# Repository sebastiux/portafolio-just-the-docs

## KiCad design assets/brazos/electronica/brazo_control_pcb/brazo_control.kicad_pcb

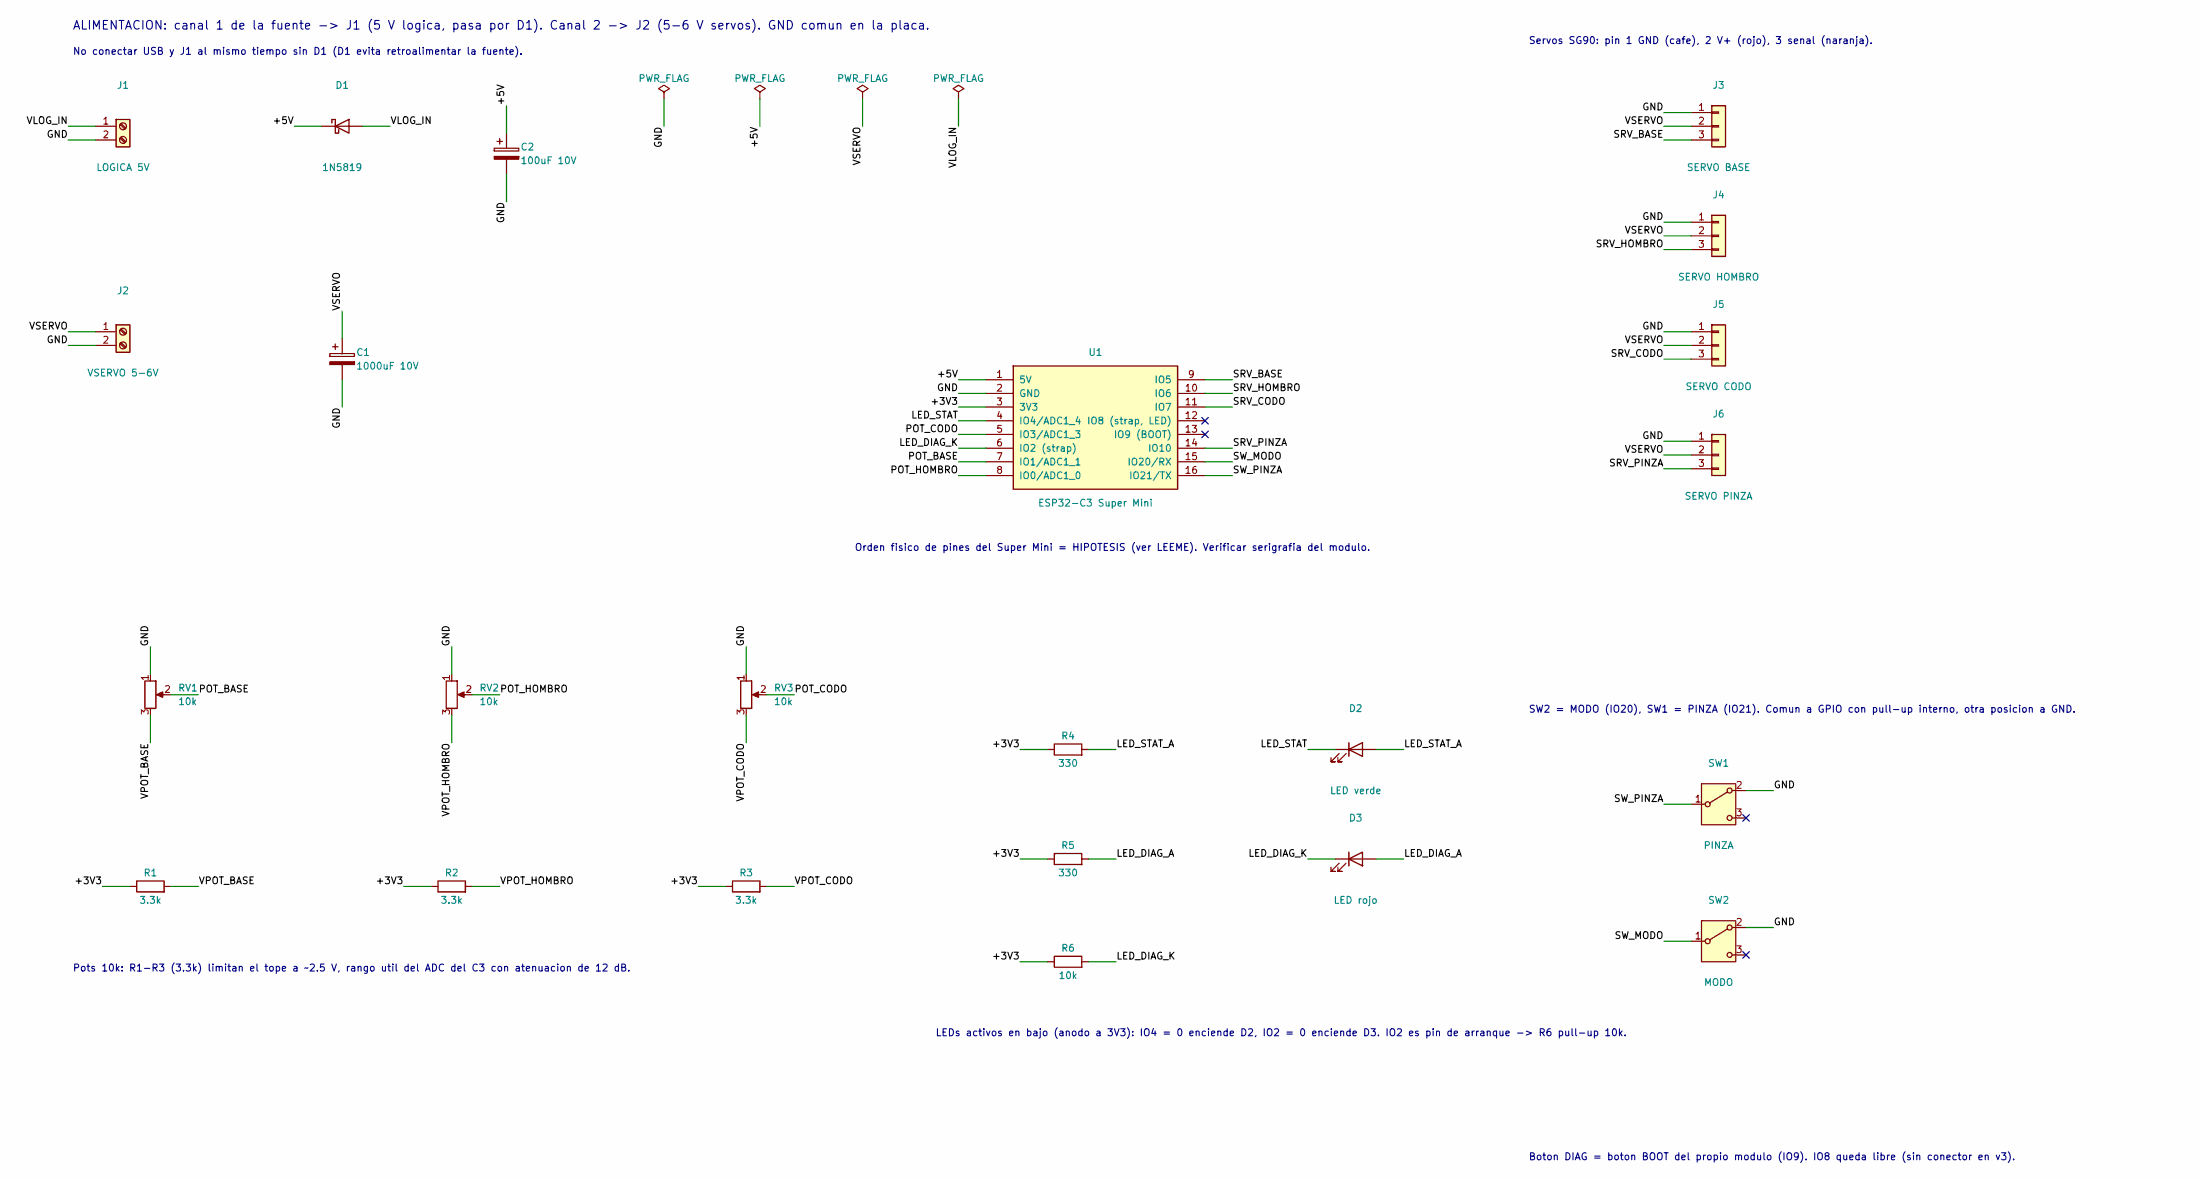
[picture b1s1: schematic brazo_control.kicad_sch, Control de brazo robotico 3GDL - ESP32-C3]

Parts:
C1: 1000uF 10V; CP_Radial_D8.0mm_P3.50mm
C2: 100uF 10V; CP_Radial_D5.0mm_P2.50mm
D1: 1N5819; D_DO-41_SOD81_P7.62mm_Horizontal
D2: LED verde; LED_D3.0mm
D3: LED rojo; LED_D3.0mm
J1: LOGICA 5V; TerminalBlock_bornier-2_P5.08mm
J2: VSERVO 5-6V; TerminalBlock_bornier-2_P5.08mm
J3: SERVO BASE; PinHeader_1x03_P2.54mm_Servo
J4: SERVO HOMBRO; PinHeader_1x03_P2.54mm_Servo
J5: SERVO CODO; PinHeader_1x03_P2.54mm_Servo
J6: SERVO PINZA; PinHeader_1x03_P2.54mm_Servo
R1, R2, R3: 3.3k; R_Axial_DIN0207_L6.3mm_D2.5mm_P5.08mm_Vertical
R4, R5: 330; R_Axial_DIN0207_L6.3mm_D2.5mm_P7.62mm_Horizontal
R6: 10k; R_Axial_DIN0207_L6.3mm_D2.5mm_P7.62mm_Horizontal
RV1, RV2, RV3: 10k; Potentiometer_Alps_RK09K_Single_Vertical
SW1: PINZA; SW_Slide-03_Wuerth-WS-SLTV_10x2.5x6.4_P2.54mm
SW2: MODO; SW_Slide-03_Wuerth-WS-SLTV_10x2.5x6.4_P2.54mm
U1: ESP32-C3 Super Mini; ESP32C3_SuperMini_Socket

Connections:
+3V3: R1.1, R2.1, R3.1, R4.1, R5.1, R6.1, U1.3 (3V3)
+5V: C2.1, D1.1 (K), U1.1 (5V)
GND: C1.2, C2.2, J1.2, J2.2, J3.1, J4.1, J5.1, J6.1, RV1.1, RV2.1, RV3.1, SW1.2 (A), SW2.2 (A), U1.2 (GND)
LED_DIAG_A: D3.2 (A), R5.2
LED_DIAG_K: D3.1 (K), R6.2, U1.6 (IO2 (strap))
LED_STAT: D2.1 (K), U1.4 (IO4/ADC1_4)
LED_STAT_A: D2.2 (A), R4.2
POT_BASE: RV1.2, U1.7 (IO1/ADC1_1)
POT_CODO: RV3.2, U1.5 (IO3/ADC1_3)
POT_HOMBRO: RV2.2, U1.8 (IO0/ADC1_0)
SRV_BASE: J3.3, U1.9 (IO5)
SRV_CODO: J5.3, U1.11 (IO7)
SRV_HOMBRO: J4.3, U1.10 (IO6)
SRV_PINZA: J6.3, U1.14 (IO10)
SW_MODO: SW2.1 (B), U1.15 (IO20/RX)
SW_PINZA: SW1.1 (B), U1.16 (IO21/TX)
VLOG_IN: D1.2 (A), J1.1
VPOT_BASE: R1.2, RV1.3
VPOT_CODO: R3.2, RV3.3
VPOT_HOMBRO: R2.2, RV2.3
VSERVO: C1.1, J2.1, J3.2, J4.2, J5.2, J6.2

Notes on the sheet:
ALIMENTACION: canal 1 de la fuente -> J1 (5 V logica, pasa por D1). Canal 2 -> J2 (5-6 V servos). GND comun en la placa.
No conectar USB y J1 al mismo tiempo sin D1 (D1 evita retroalimentar la fuente).
Orden fisico de pines del Super Mini = HIPOTESIS (ver LEEME). Verificar serigrafia del modulo.
Pots 10k: R1-R3 (3.3k) limitan el tope a ~2.5 V, rango util del ADC del C3 con atenuacion de 12 dB.
LEDs activos en bajo (anodo a 3V3): IO4 = 0 enciende D2, IO2 = 0 enciende D3. IO2 es pin de arranque -> R6 pull-up 10k.
Boton DIAG = boton BOOT del propio modulo (IO9). IO8 queda libre (sin conector en v3).
SW2 = MODO (IO20), SW1 = PINZA (IO21). Comun a GPIO con pull-up interno, otra posicion a GND.
Servos SG90: pin 1 GND (cafe), 2 V+ (rojo), 3 senal (naranja).

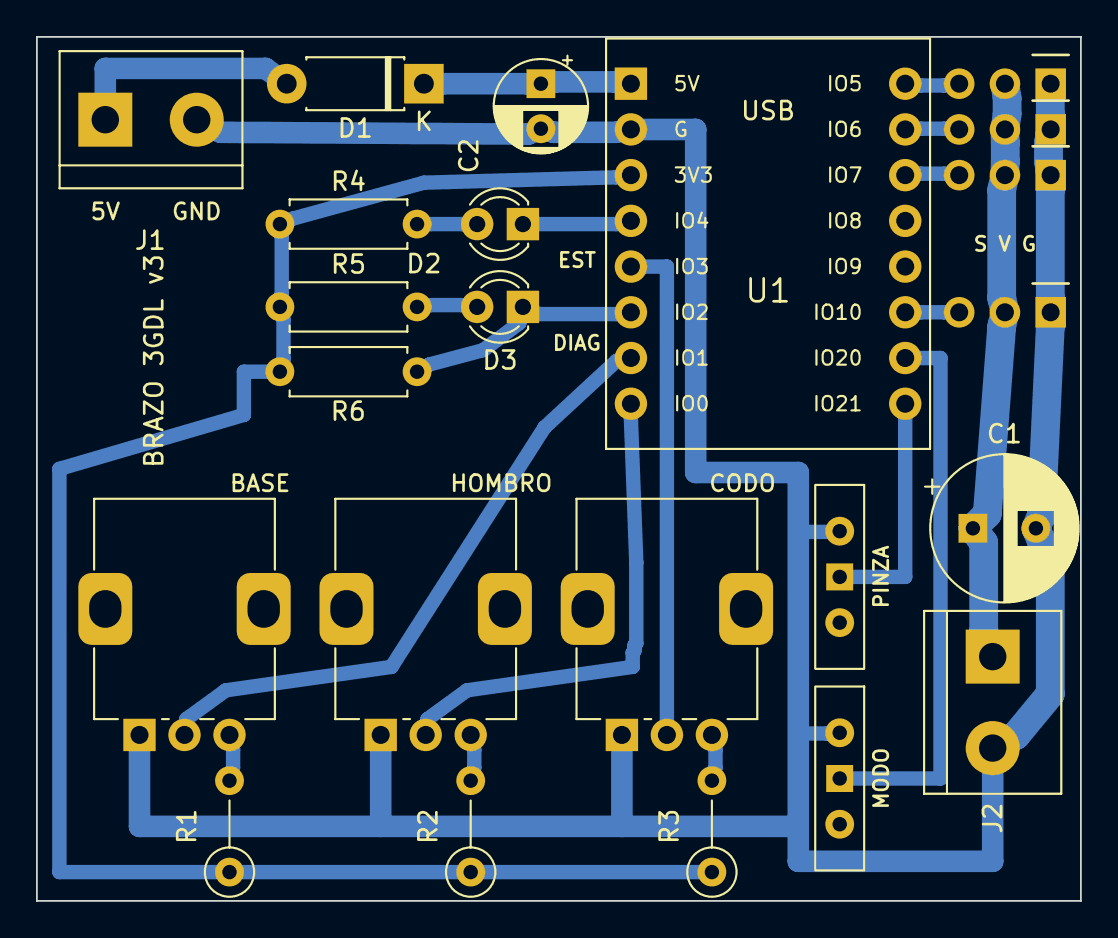
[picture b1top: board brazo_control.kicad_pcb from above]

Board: 2 copper layers, 58.0 x 48.0 mm, 23 parts (0 on the bottom side), 21 nets.

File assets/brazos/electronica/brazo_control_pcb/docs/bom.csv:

Cantidad,Referencias,Valor,Footprint,Funcion
1,U1,ESP32-C3 Super Mini,ESP32C3_SuperMini_Socket,Modulo en zocalo 2x(1x08) hembra
1,J1,LOGICA 5V,TerminalBlock_bornier-2_P5.08mm,Bornera canal 1 fuente: logica
1,J2,VSERVO 5-6V,TerminalBlock_bornier-2_P5.08mm,Bornera canal 2 fuente: servos
1,D1,1N5819,D_DO-41_SOD81_P7.62mm_Horizontal,Schottky: polaridad inversa y retroalimentacion USB
1,C1,1000uF 10V,CP_Radial_D8.0mm_P3.50mm,Bulk servos
1,C2,100uF 10V,CP_Radial_D5.0mm_P2.50mm,Bulk ESP32 (picos WiFi)
1,J3,SERVO BASE,PinHeader_1x03_P2.54mm_Servo,GND V+ SIG
1,J4,SERVO HOMBRO,PinHeader_1x03_P2.54mm_Servo,GND V+ SIG
1,J5,SERVO CODO,PinHeader_1x03_P2.54mm_Servo,GND V+ SIG
1,J6,SERVO PINZA,PinHeader_1x03_P2.54mm_Servo,GND V+ SIG
3,RV1 RV2 RV3,10k,Potentiometer_Alps_RK09K_Single_Vertical,Pot base; Pot hombro; Pot codo
3,R1 R2 R3,3.3k,R_Axial_DIN0207_L6.3mm_D2.5mm_P5.08mm_Vertical,Limita tope de RV1 a ~2.5 V; Limita tope de RV2 a ~2.5 V; Limita tope de RV3 a ~2.5 V
2,R4 R5,330,R_Axial_DIN0207_L6.3mm_D2.5mm_P7.62mm_Horizontal,LED estado; LED diagnostico
1,R6,10k,R_Axial_DIN0207_L6.3mm_D2.5mm_P7.62mm_Horizontal,Pull-up GPIO2 (strapping)
1,D2,LED verde,LED_D3.0mm,Estado (activo en bajo)
1,D3,LED rojo,LED_D3.0mm,Diagnostico
1,SW1,PINZA,SW_Slide-03_Wuerth-WS-SLTV_10x2.5x6.4_P2.54mm,Abrir/cerrar pinza (manual)
1,SW2,MODO,SW_Slide-03_Wuerth-WS-SLTV_10x2.5x6.4_P2.54mm,Manual / App WiFi

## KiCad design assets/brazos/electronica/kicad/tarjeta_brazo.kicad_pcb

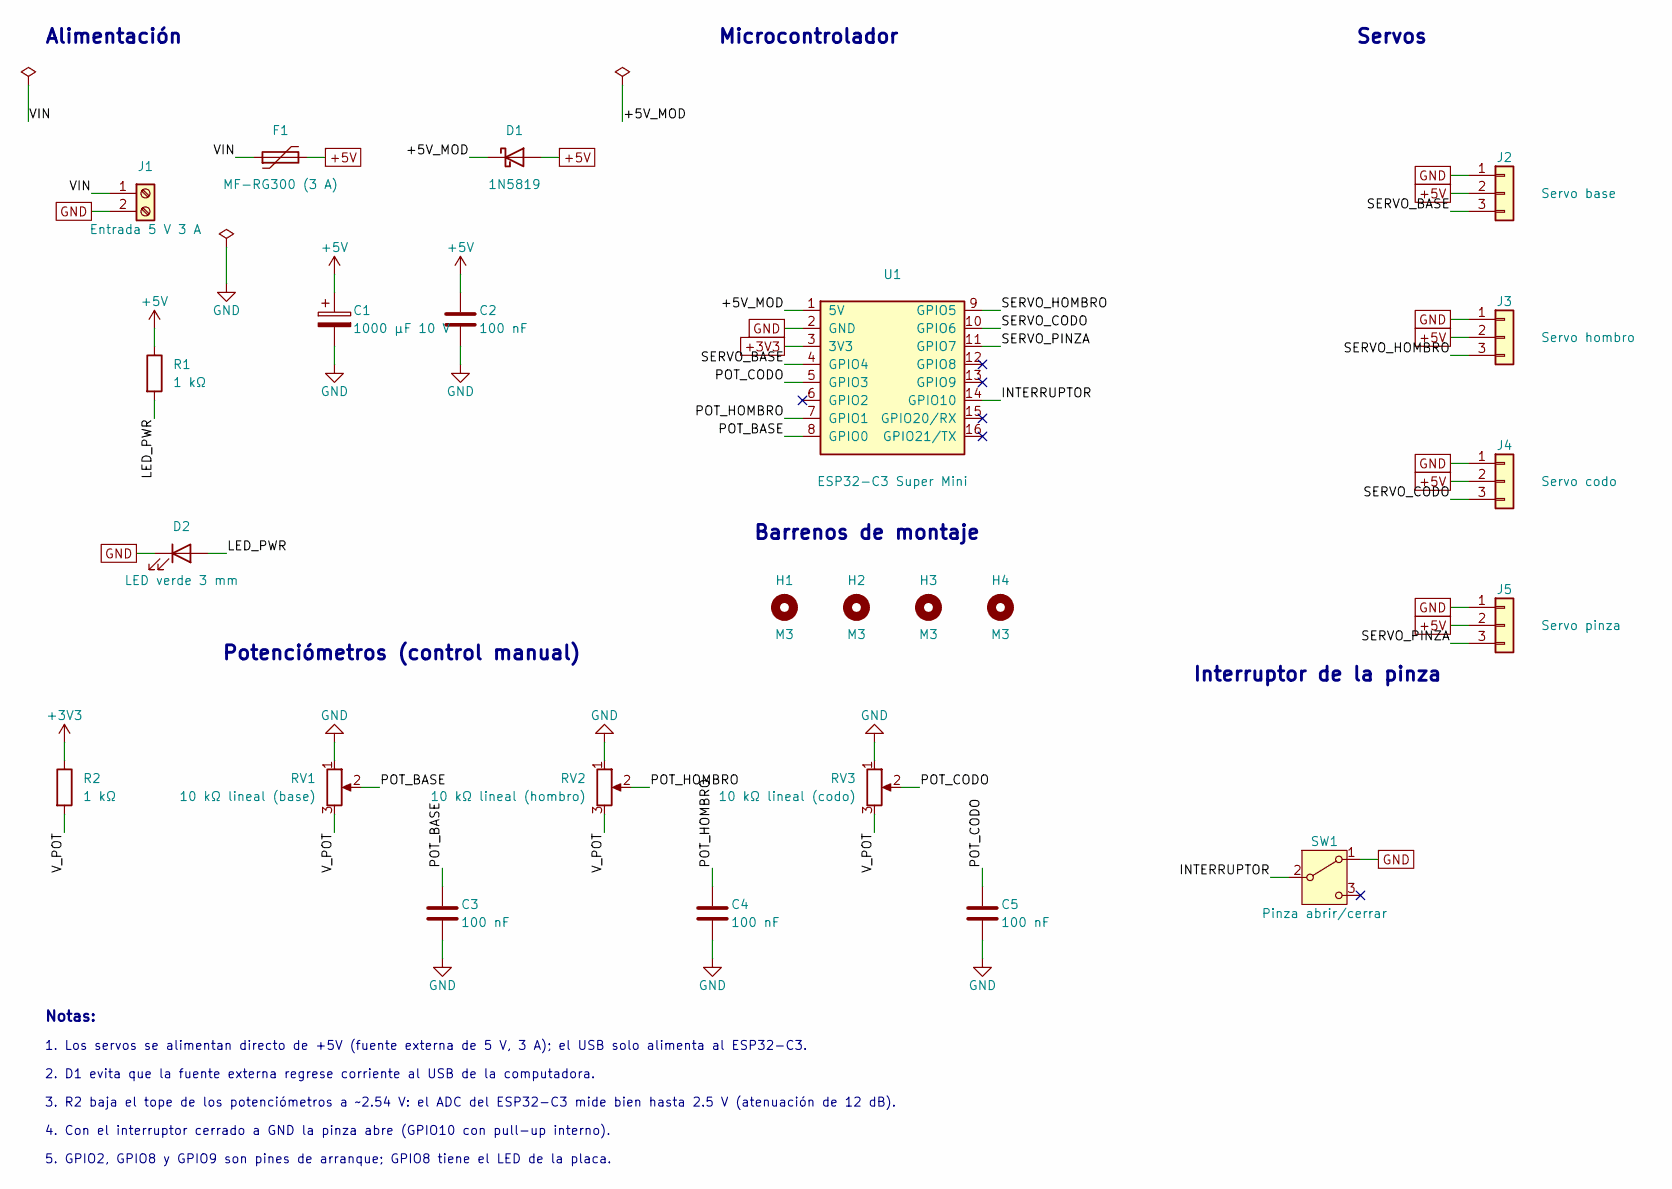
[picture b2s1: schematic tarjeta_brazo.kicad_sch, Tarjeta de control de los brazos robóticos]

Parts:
C1: 1000 µF 10 V; CP_Radial_D10.0mm_P5.00mm
C2, C3, C4, C5: 100 nF; C_Disc_D5.0mm_W2.5mm_P5.00mm
D1: 1N5819; D_DO-41_SOD81_P10.16mm_Horizontal
D2: LED verde 3 mm; LED_D3.0mm
F1: MF-RG300 (3 A); Fuse_Bourns_MF-RG300
H1, H2, H3, H4: M3; MountingHole_3.2mm_M3
J1: Entrada 5 V 3 A; TerminalBlock_Phoenix_MKDS-1,5-2_1x02_P5.00mm_Horizontal
J2: Servo base; PinHeader_1x03_P2.54mm_Vertical
J3: Servo hombro; PinHeader_1x03_P2.54mm_Vertical
J4: Servo codo; PinHeader_1x03_P2.54mm_Vertical
J5: Servo pinza; PinHeader_1x03_P2.54mm_Vertical
R1, R2: 1 kΩ; R_Axial_DIN0207_L6.3mm_D2.5mm_P10.16mm_Horizontal
RV1: 10 kΩ lineal (base); Potentiometer_Alps_RK09K_Single_Vertical
RV2: 10 kΩ lineal (hombro); Potentiometer_Alps_RK09K_Single_Vertical
RV3: 10 kΩ lineal (codo); Potentiometer_Alps_RK09K_Single_Vertical
SW1: Pinza abrir/cerrar; SW_Slide_SPDT_Straight_CK_OS102011MS2Q
U1: ESP32-C3 Super Mini; ESP32-C3_SuperMini

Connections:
+3V3: R2.1, U1.3 (3V3)
+5V: C1.1, C2.1, D1.2 (A), F1.2, J2.2, J3.2, J4.2, J5.2, R1.1
+5V_MOD: D1.1 (K), U1.1 (5V)
GND: C1.2, C2.2, C3.2, C4.2, C5.2, D2.1 (K), J1.2, J2.1, J3.1, J4.1, J5.1, RV1.1, RV2.1, RV3.1, SW1.1 (A), U1.2 (GND)
INTERRUPTOR: SW1.2 (B), U1.14 (GPIO10)
LED_PWR: D2.2 (A), R1.2
POT_BASE: C3.1, RV1.2, U1.8 (GPIO0)
POT_CODO: C5.1, RV3.2, U1.5 (GPIO3)
POT_HOMBRO: C4.1, RV2.2, U1.7 (GPIO1)
SERVO_BASE: J2.3, U1.4 (GPIO4)
SERVO_CODO: J4.3, U1.10 (GPIO6)
SERVO_HOMBRO: J3.3, U1.9 (GPIO5)
SERVO_PINZA: J5.3, U1.11 (GPIO7)
VIN: F1.1, J1.1
V_POT: R2.2, RV1.3, RV2.3, RV3.3

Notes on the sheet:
Alimentación
Microcontrolador
Servos
Potenciómetros (control manual)
Interruptor de la pinza
Barrenos de montaje
Notas:
1. Los servos se alimentan directo de +5V (fuente externa de 5 V, 3 A); el USB solo alimenta al ESP32-C3.
2. D1 evita que la fuente externa regrese corriente al USB de la computadora.
3. R2 baja el tope de los potenciómetros a ~2.54 V: el ADC del ESP32-C3 mide bien hasta 2.5 V (atenuación de 12 dB).
4. Con el interruptor cerrado a GND la pinza abre (GPIO10 con pull-up interno).
5. GPIO2, GPIO8 y GPIO9 son pines de arranque; GPIO8 tiene el LED de la placa.

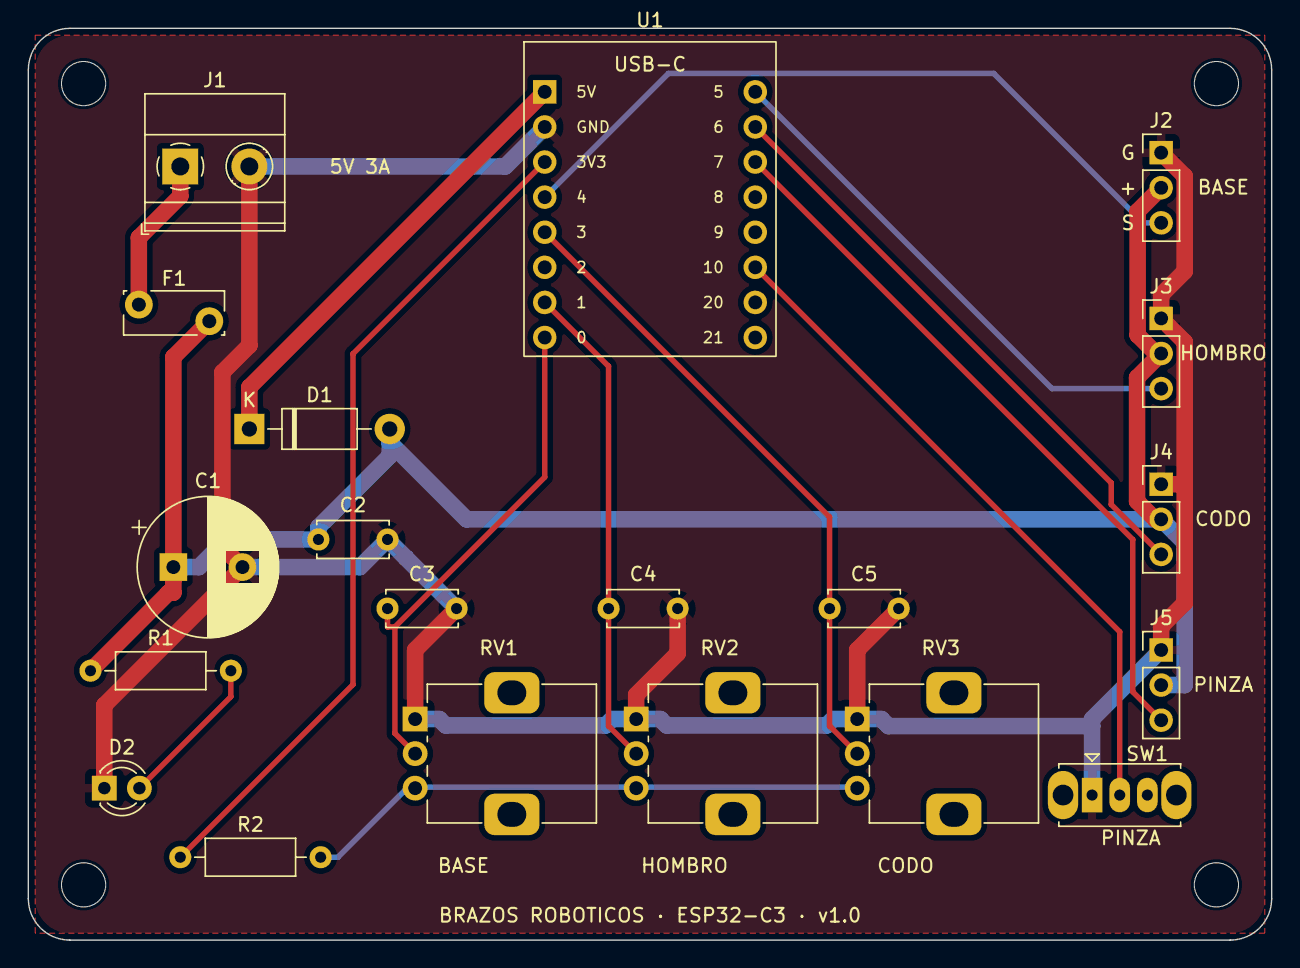
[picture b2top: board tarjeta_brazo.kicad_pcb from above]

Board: 2 copper layers, 90.0 x 66.0 mm, 24 parts (0 on the bottom side), 15 nets.

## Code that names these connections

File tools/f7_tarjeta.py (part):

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# ---------------------------------------------------------------------------
# Componentes: referencia -> (símbolo, valor, huella, {pin: red})
# Pines del ESP32-C3 Super Mini con el USB-C hacia arriba:
#   izquierda 1-8:  5V GND 3V3 GPIO4 GPIO3 GPIO2 GPIO1 GPIO0
#   derecha  9-16:  GPIO5 GPIO6 GPIO7 GPIO8 GPIO9 GPIO10 GPIO20 GPIO21
# ---------------------------------------------------------------------------
NC = None
NETLIST = {
    "U1": ("brazo:ESP32-C3_SuperMini", "ESP32-C3 Super Mini", "brazo:ESP32-C3_SuperMini",
           {"1": "+5V_MOD", "2": "GND", "3": "+3V3", "4": "SERVO_BASE", "5": "POT_CODO",
            "6": NC, "7": "POT_HOMBRO", "8": "POT_BASE",
            "9": "SERVO_HOMBRO", "10": "SERVO_CODO", "11": "SERVO_PINZA", "12": NC,
            "13": NC, "14": "INTERRUPTOR", "15": NC, "16": NC}),
    "J1": ("Connector:Screw_Terminal_01x02", "Entrada 5 V 3 A",
           "TerminalBlock_Phoenix:TerminalBlock_Phoenix_MKDS-1,5-2_1x02_P5.00mm_Horizontal",
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    "J4": ("Connector_Generic:Conn_01x03", "Servo codo", "Connector_PinHeader_2.54mm:PinHeader_1x03_P2.54mm_Vertical",
           {"1": "GND", "2": "+5V", "3": "SERVO_CODO"}),
    "J5": ("Connector_Generic:Conn_01x03", "Servo pinza", "Connector_PinHeader_2.54mm:PinHeader_1x03_P2.54mm_Vertical",
           {"1": "GND", "2": "+5V", "3": "SERVO_PINZA"}),
    "RV1": ("Device:R_Potentiometer", "10 kΩ lineal (base)", "Potentiometer_THT:Potentiometer_Alps_RK09K_Single_Vertical",
            {"1": "GND", "2": "POT_BASE", "3": "V_POT"}),
    "RV2": ("Device:R_Potentiometer", "10 kΩ lineal (hombro)", "Potentiometer_THT:Potentiometer_Alps_RK09K_Single_Vertical",
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# ---------------------------------------------------------------------------
PINES_MODULO = [
    ("1", "5V", "power_in"), ("2", "GND", "power_in"), ("3", "3V3", "power_out"),
    ("4", "GPIO4", "bidirectional"), ("5", "GPIO3", "bidirectional"), ("6", "GPIO2", "bidirectional"),
    ("7", "GPIO1", "bidirectional"), ("8", "GPIO0", "bidirectional"),
    ("9", "GPIO5", "bidirectional"), ("10", "GPIO6", "bidirectional"), ("11", "GPIO7", "bidirectional"),
    ("12", "GPIO8", "bidirectional"), ("13", "GPIO9", "bidirectional"), ("14", "GPIO10", "bidirectional"),
    ("15", "GPIO20/RX", "bidirectional"), ("16", "GPIO21/TX", "bidirectional"),
]

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
BLOQUES = [
    ("Alimentación", 20, 30), ("Microcontrolador", 115, 30), ("Servos", 205, 30),
    ("Potenciómetros (control manual)", 45, 117), ("Interruptor de la pinza", 182, 120),
    ("Barrenos de montaje", 120, 100),
]

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        "1. Los servos se alimentan directo de +5V (fuente externa de 5 V, 3 A); el USB solo alimenta al ESP32-C3.",
        "2. D1 evita que la fuente externa regrese corriente al USB de la computadora.",
        "3. R2 baja el tope de los potenciómetros a ~2.54 V: el ADC del ESP32-C3 mide bien hasta 2.5 V (atenuación de 12 dB).",
        "4. Con el interruptor cerrado a GND la pinza abre (GPIO10 con pull-up interno).",
        "5. GPIO2, GPIO8 y GPIO9 son pines de arranque; GPIO8 tiene el LED de la placa.",
    ]
    for i, n in enumerate(notas):
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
